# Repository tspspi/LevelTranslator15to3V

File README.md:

# Level shifter for +-15V to 0-3.3V analog signals (low frequency)

A simple level shifter for +-15V analog low frequency signals
to 0-3.3V range.

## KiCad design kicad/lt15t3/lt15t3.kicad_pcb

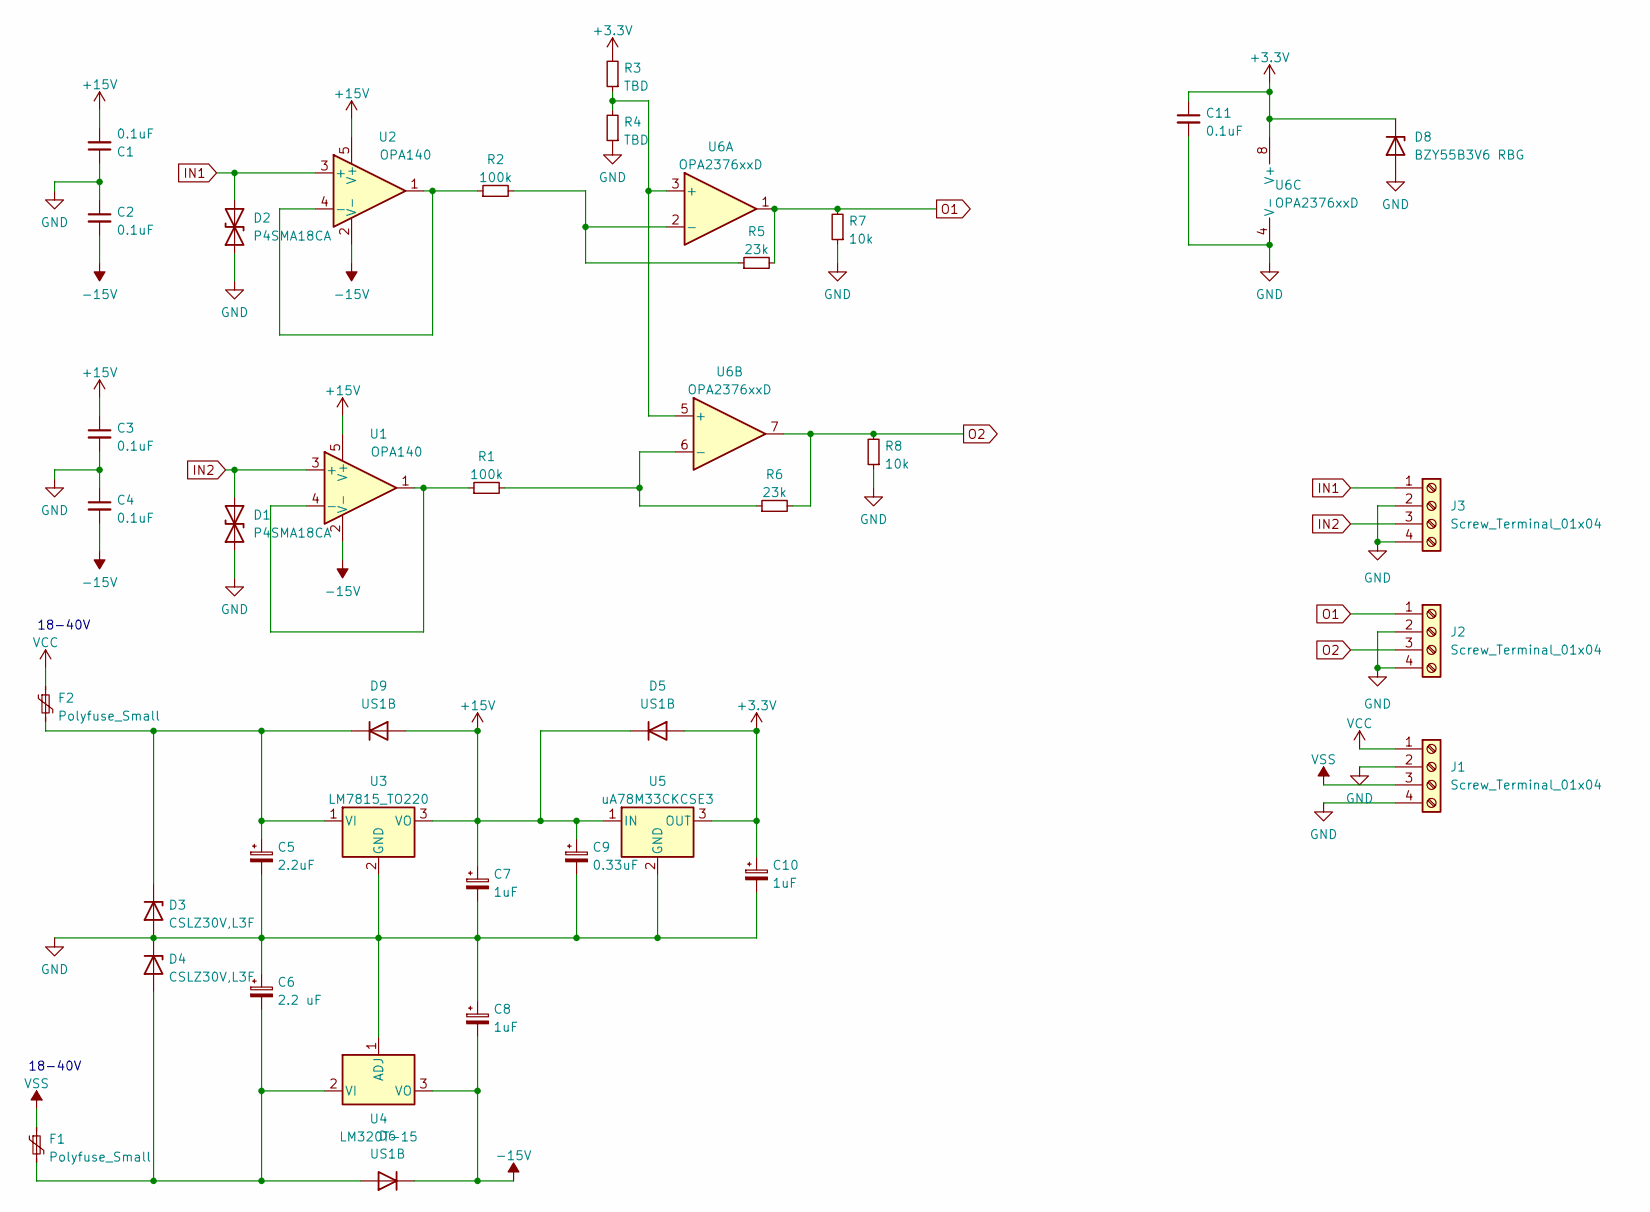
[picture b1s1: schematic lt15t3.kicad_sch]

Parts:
C1, C2, C3, C4, C11: 0.1uF; C_0805_2012Metric
C5: 2.2uF; C_1206_3216Metric
C6: 2.2 uF; C_1206_3216Metric
C7, C8, C10: 1uF; C_0805_2012Metric
C9: 0.33uF; C_0805_2012Metric
D1, D2: P4SMA18CA; D_SMA
D3, D4: CSLZ30V,L3F; D_0603_1608Metric
D5, D6, D9: US1B; D_SMA
D8: BZY55B3V6 RBG; D_0805_2012Metric
F1, F2: Polyfuse_Small; C_Disc_D5.1mm_W3.2mm_P5.00mm
J1, J2, J3: Screw_Terminal_01x04; PinHeader_1x04_P2.54mm_Vertical
R1, R2: 100k; R_0805_2012Metric
R3, R4: TBD; R_0805_2012Metric
R5, R6: 23k; R_0805_2012Metric
R7, R8: 10k; R_0805_2012Metric
U1, U2: OPA140; TSOT-23-5
U3: LM7815_TO220; TO-220-3_Vertical
U4: LM320T-15; TO-220-3_Vertical
U5: uA78M33CKCSE3; TO-220-3_Vertical
U6: OPA2376xxD; SOIC-8W_5.3x5.3mm_P1.27mm

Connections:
+3.3V: C10.1, C11.1, D5.2 (A), D8.1 (K), R3.2, U5.3 (OUT), U6.8 (V+)
+15V: C1.2, C3.1, C7.1, C9.1, D5.1 (K), D9.2 (A), U1.5 (V+), U2.5 (V+), U3.3 (VO), U5.1 (IN)
-15V: C2.2, C4.2, C8.2, D6.1 (K), U1.2 (V-), U2.2 (V-), U4.3 (VO)
GND: C1.1, C2.1, C3.2, C4.1, C5.2, C6.1, C7.2, C8.1, C9.2, C10.2, C11.2, D1.1 (A1), D2.1 (A1), D3.2 (A), D4.1 (K), D8.2 (A), J1.2, J1.4, J2.2, J2.4, J3.2, J3.4, R4.1, R7.1, R8.1, U3.2 (GND), U4.1 (ADJ), U5.2 (GND), U6.4 (V-)
IN1: D2.2 (A2), J3.1, U2.3 (+)
IN2: D1.2 (A2), J3.3, U1.3 (+)
unnamed: C5.1, D3.1 (K), D9.1 (K), F2.2, U3.1 (VI)
unnamed: C6.2, D4.2 (A), D6.2 (A), F1.2, U4.2 (VI)
unnamed: R1.1, U1.1, U1.4 (-)
unnamed: R2.1, U2.1, U2.4 (-)
unnamed: R3.1, R4.2, U6.3 (+), U6.5 (+)
unnamed: R2.2, R5.1, U6.2 (-)
unnamed: R1.2, R6.1, U6.6 (-)
O1: J2.1, R5.2, R7.2, U6.1
O2: J2.3, R6.2, R8.2, U6.7
VCC: F2.1, J1.1
VSS: F1.1, J1.3

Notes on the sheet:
18-40V

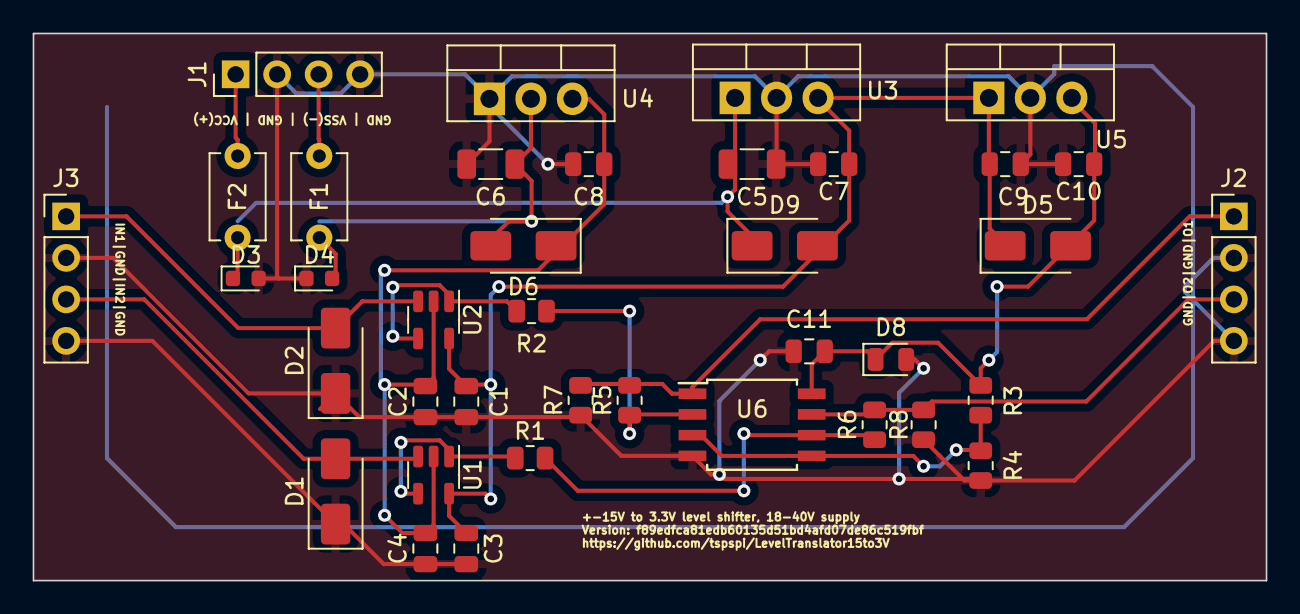
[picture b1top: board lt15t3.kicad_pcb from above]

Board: 2 copper layers, 75.5 x 33.5 mm, 38 parts (0 on the bottom side), 17 nets.

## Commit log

2023-09-04 Finalize PCB design
2023-09-04 Adding commit hash to PCB design
2023-09-05 Add missing mounting holes
2023-09-05 Adding readme
